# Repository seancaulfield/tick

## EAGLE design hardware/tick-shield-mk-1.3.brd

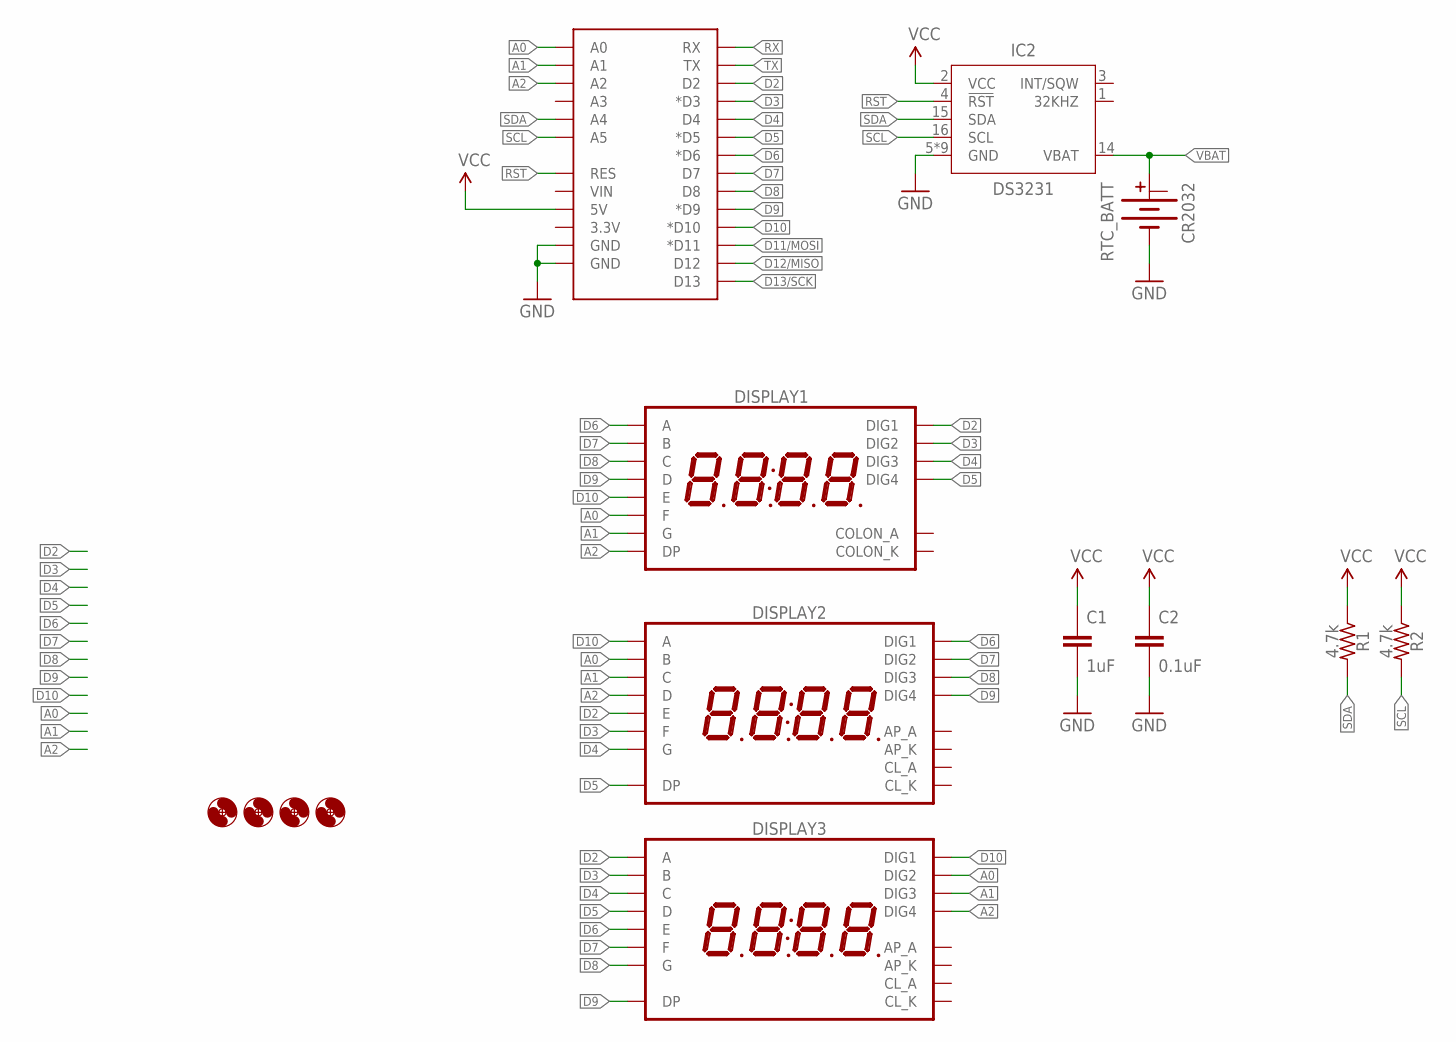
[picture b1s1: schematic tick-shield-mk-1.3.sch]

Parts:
C1: 1uF; C025-024X044
C2: 0.1uF; C025-024X044
DISPLAY1: 7SEG_4DIGIT_COLON14.2MM-CC-NS; 7SEG_4DIG_NS
DISPLAY2, DISPLAY3: 7SEG_4DIGIT_COLON_APOS; 7SEG_4DIG_10MM
H1, H2, H3, H4: HOLE#2; HOLE-#2
IC2: DS3231; SO16W
R1, R2: 4.7k; RESISTOR-AXIAL-PTH-6.35MM
RTC_BATT: CR2032; BATTCON_20MM_MINE
U$1: ARDUINO_SHIELD_SMALLER; ARDUINO_SHIELD_NOOUTLINE_INSIDE_SMALLER

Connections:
A0: DISPLAY1.P$12 (F), DISPLAY2.16 (B), DISPLAY3.2 (DIG2), U$1.A0
A1: DISPLAY1.P$5 (G), DISPLAY2.13 (C), DISPLAY3.6 (DIG3), U$1.A1
A2: DISPLAY1.P$3 (DP), DISPLAY2.3 (D), DISPLAY3.8 (DIG4), U$1.A2
D2: DISPLAY1.P$14 (DIG1), DISPLAY2.5 (E), DISPLAY3.14 (A), U$1.D2
D3: DISPLAY1.P$11 (DIG2), DISPLAY2.11 (F), DISPLAY3.16 (B), U$1.D3 (*D3)
D4: DISPLAY1.P$10 (DIG3), DISPLAY2.15 (G), DISPLAY3.13 (C), U$1.D4
D5: DISPLAY1.P$6 (DIG4), DISPLAY2.7 (DP), DISPLAY3.3 (D), U$1.D5 (*D5)
D6: DISPLAY1.P$13 (A), DISPLAY2.1 (DIG1), DISPLAY3.5 (E), U$1.D6 (*D6)
D7: DISPLAY1.P$9 (B), DISPLAY2.2 (DIG2), DISPLAY3.11 (F), U$1.D7
D8: DISPLAY1.P$4 (C), DISPLAY2.6 (DIG3), DISPLAY3.15 (G), U$1.D8
D9: DISPLAY1.P$2 (D), DISPLAY2.8 (DIG4), DISPLAY3.7 (DP), U$1.D9 (*D9)
D10: DISPLAY1.P$1 (E), DISPLAY2.14 (A), DISPLAY3.1 (DIG1), U$1.D10 (*D10)
D11/MOSI: U$1.D11 (*D11)
D12/MISO: U$1.D12
D13/SCK: U$1.D13
GND: C1.2, C2.2, IC2.5 (GND), IC2.6 (GND), IC2.7 (GND), IC2.8 (GND), IC2.9 (GND), IC2.10 (GND), IC2.11 (GND), IC2.12 (GND), IC2.13 (GND), RTC_BATT.BOTTOM (-), U$1.GND@0 (GND), U$1.GND@1 (GND)
RST: IC2.4 (!RST), U$1.RES
RX: U$1.RX
SCL: IC2.16 (SCL), R2.P$2 (2), U$1.A5
SDA: IC2.15 (SDA), R1.P$2 (2), U$1.A4
TX: U$1.TX
VBAT: IC2.14 (VBAT), RTC_BATT.TOP@1 (+)
VCC: C1.1, C2.1, IC2.2 (VCC), R1.P$1 (1), R2.P$1 (1), U$1.5V

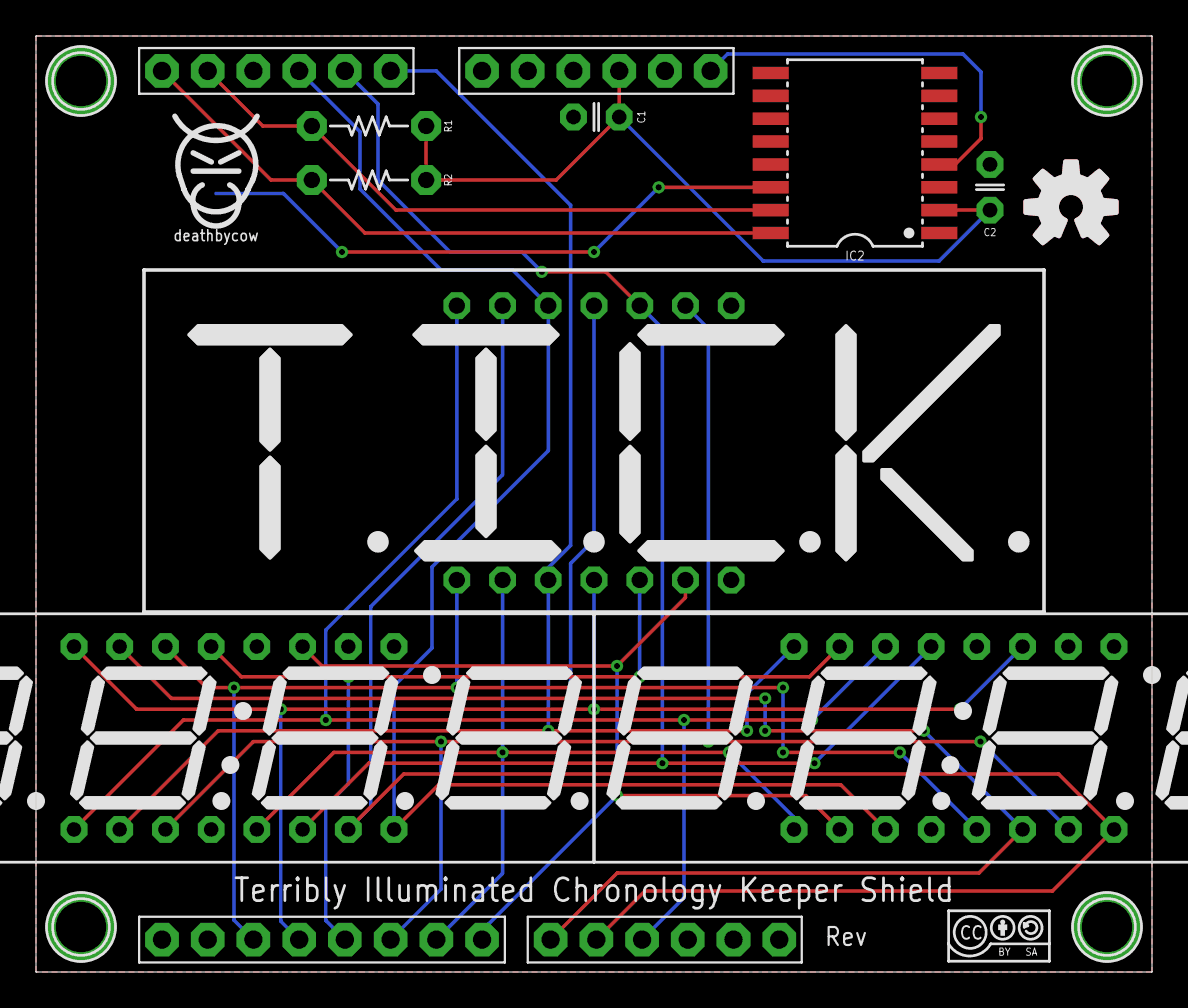
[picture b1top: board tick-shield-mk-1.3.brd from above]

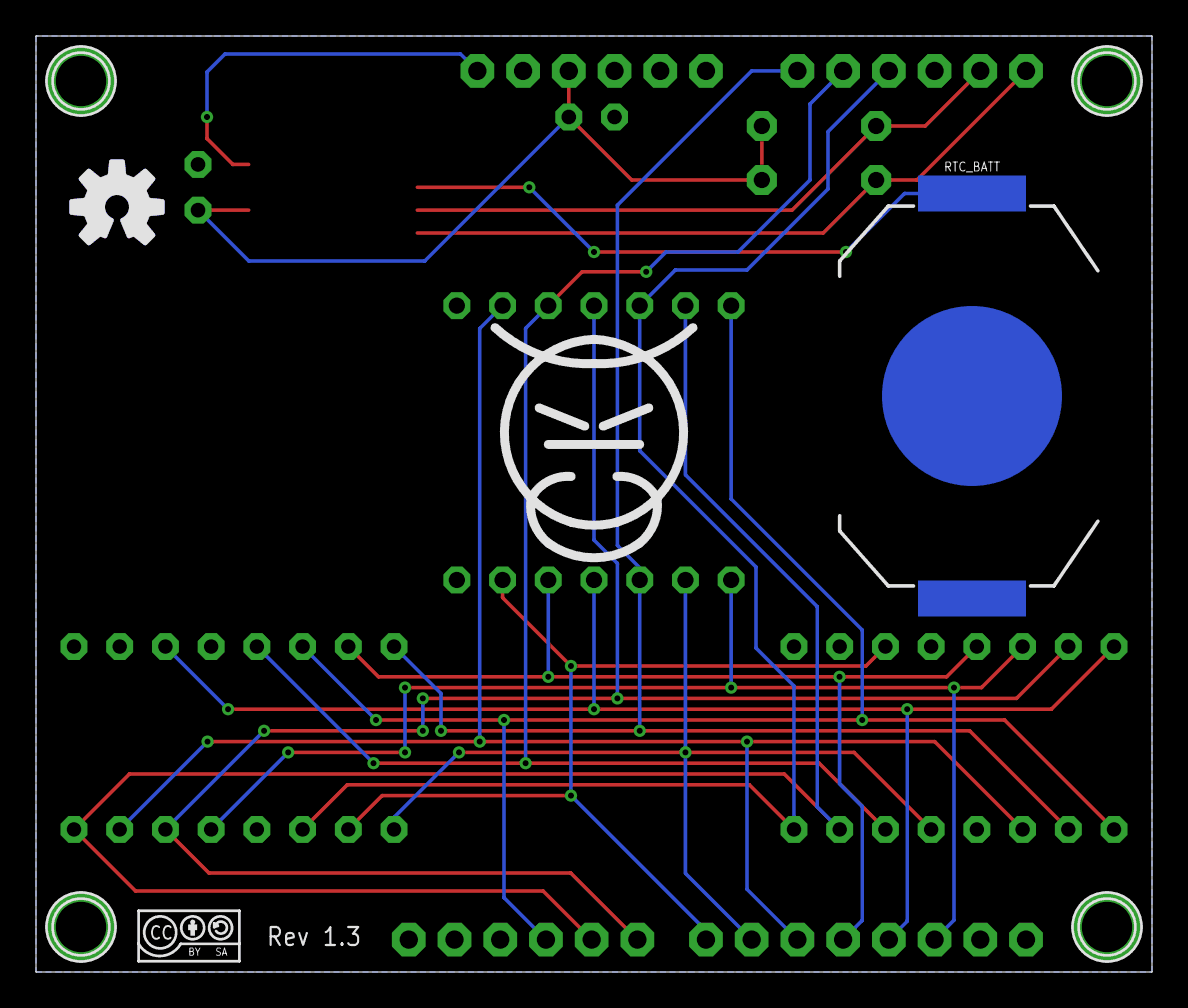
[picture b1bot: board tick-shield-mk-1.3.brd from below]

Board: 2 copper layers, 62.0 x 52.0 mm, 21 parts (4 on the bottom side), 18 nets.

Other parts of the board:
U$2: TICK_SYMBOL_0.56
U$3, U$4: CC-BY-SA-4.0-NO-URL
U$5: COW
U$6: COW_SMALL
U$7, U$8: OSHWLOGO_TOP_0.2_A

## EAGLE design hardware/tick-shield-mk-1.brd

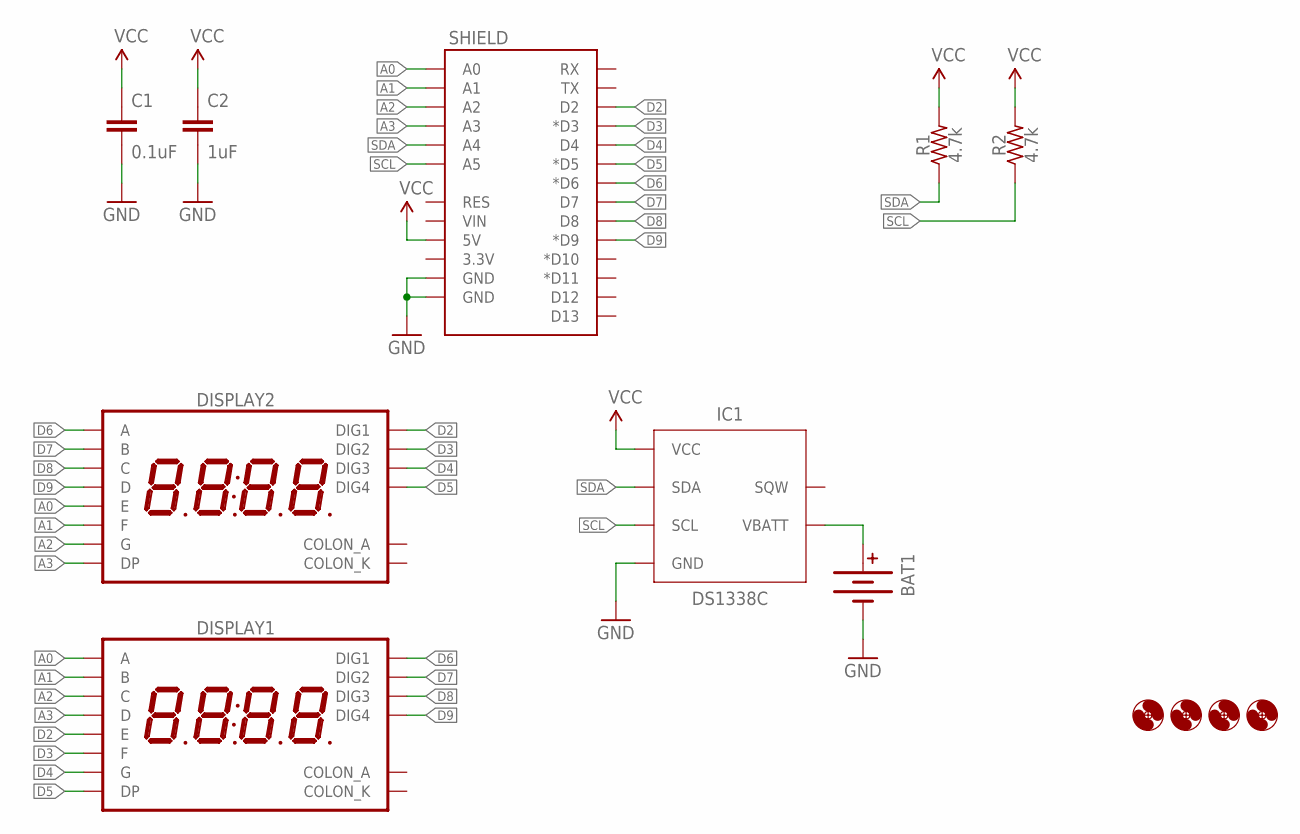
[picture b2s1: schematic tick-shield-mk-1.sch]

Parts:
BAT1: BATTERY12MM; BATTCON_12MM
C1: 0.1uF; C0603
C2: 1uF; C0805
DISPLAY1, DISPLAY2: 7SEG_4DIGIT_COLON14.2MM-CC; 7SEG_4DIG_0.56IN_14MM_ADAFRUIT
H1, H2, H3, H4: HOLE#2; HOLE-#2
IC1: DS1338C; SO16W
R1, R2: 4.7k; R0603
SHIELD: ARDUINO_SHIELD_SMALLER; ARDUINO_SHIELD_NOOUTLINE_INSIDE_SMALLER

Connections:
A0: DISPLAY1.P$13 (A), DISPLAY2.P$1 (E), SHIELD.A0
A1: DISPLAY1.P$9 (B), DISPLAY2.P$12 (F), SHIELD.A1
A2: DISPLAY1.P$4 (C), DISPLAY2.P$5 (G), SHIELD.A2
A3: DISPLAY1.P$2 (D), DISPLAY2.P$3 (DP), SHIELD.A3
D2: DISPLAY1.P$1 (E), DISPLAY2.P$14 (DIG1), SHIELD.D2
D3: DISPLAY1.P$12 (F), DISPLAY2.P$11 (DIG2), SHIELD.D3 (*D3)
D4: DISPLAY1.P$5 (G), DISPLAY2.P$10 (DIG3), SHIELD.D4
D5: DISPLAY1.P$3 (DP), DISPLAY2.P$6 (DIG4), SHIELD.D5 (*D5)
D6: DISPLAY1.P$14 (DIG1), DISPLAY2.P$13 (A), SHIELD.D6 (*D6)
D7: DISPLAY1.P$11 (DIG2), DISPLAY2.P$9 (B), SHIELD.D7
D8: DISPLAY1.P$10 (DIG3), DISPLAY2.P$4 (C), SHIELD.D8
D9: DISPLAY1.P$6 (DIG4), DISPLAY2.P$2 (D), SHIELD.D9 (*D9)
GND: BAT1.GND (-), C1.2, C2.2, IC1.4 (GND), IC1.5 (GND), IC1.6 (GND), IC1.7 (GND), IC1.8 (GND), IC1.9 (GND), IC1.10 (GND), IC1.11 (GND), IC1.12 (GND), IC1.13 (GND), IC1.15 (GND), SHIELD.GND@0 (GND), SHIELD.GND@1 (GND)
unnamed: BAT1.PWR@1 (+), IC1.14 (VBATT)
SCL: IC1.1 (SCL), R2.1, SHIELD.A5
SDA: IC1.16 (SDA), R1.1, SHIELD.A4
VCC: C1.1, C2.1, IC1.3 (VCC), R1.2, R2.2, SHIELD.5V

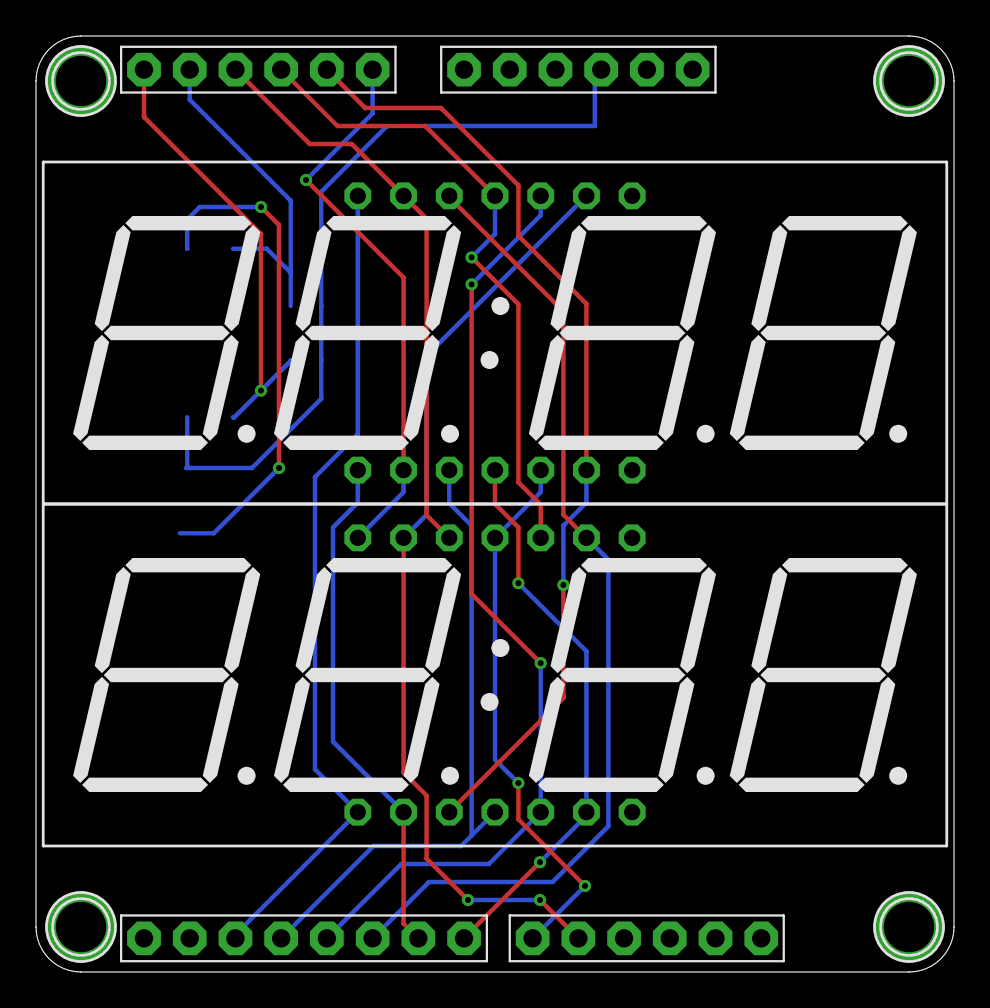
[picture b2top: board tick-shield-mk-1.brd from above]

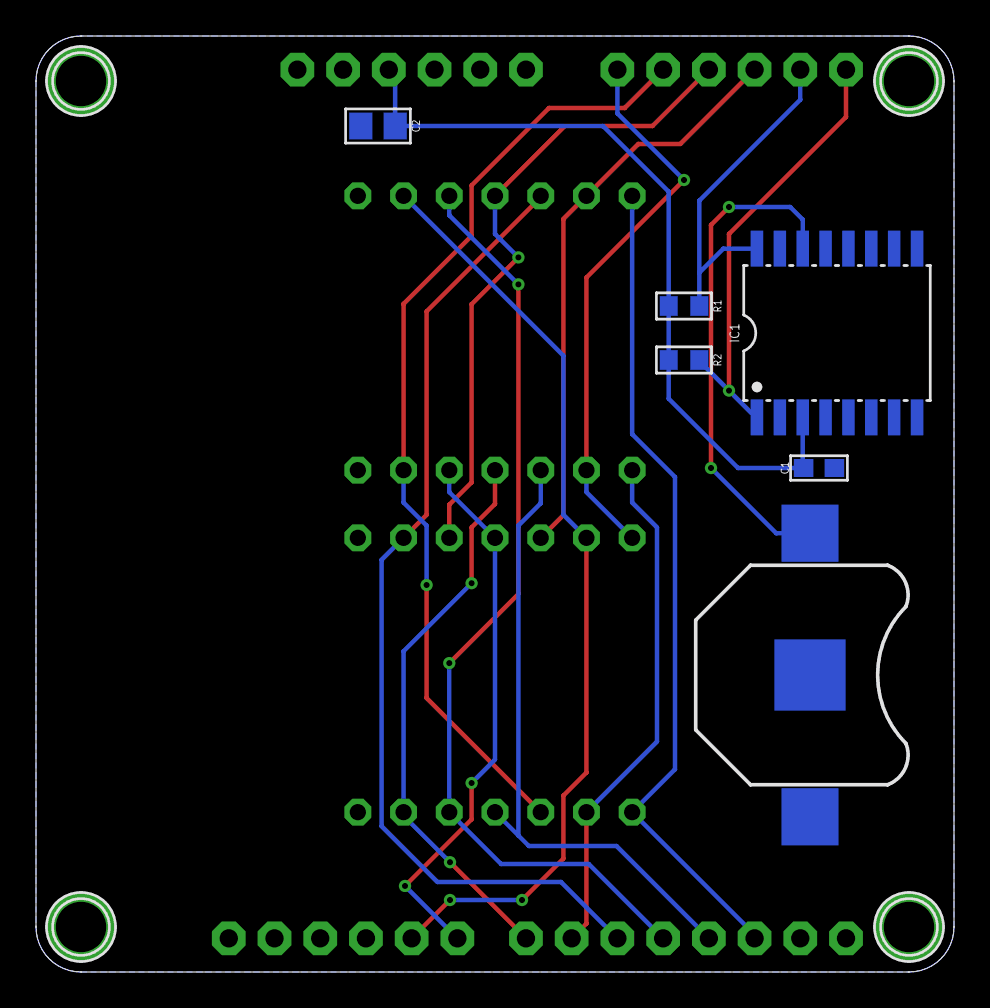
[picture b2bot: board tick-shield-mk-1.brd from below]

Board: 2 copper layers, 51.0 x 52.0 mm, 13 parts (6 on the bottom side), 17 nets.

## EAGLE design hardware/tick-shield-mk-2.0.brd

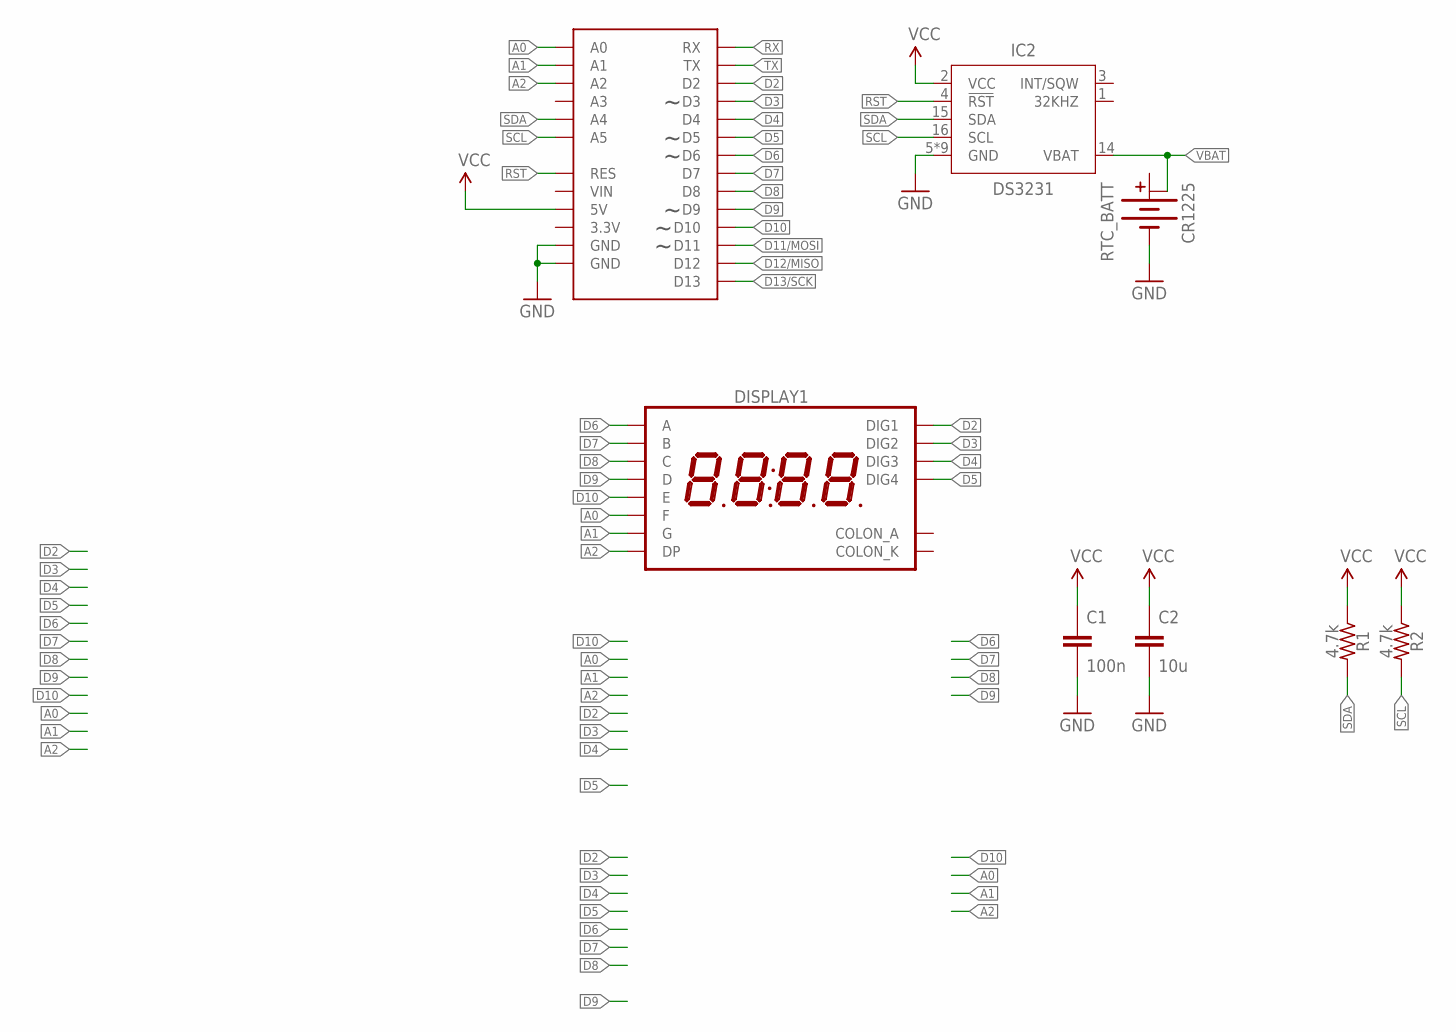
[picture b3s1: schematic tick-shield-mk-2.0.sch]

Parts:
C1: 100n; C025-024X044
C2: 10u; C050-025X075
DISPLAY1: 7SEG_4DIGIT_COLONTICK; 7SEG_4DIG_TICK
IC2: DS3231; SO16W
R1, R2: 4.7k; RESISTOR-AXIAL-PTH-7.62MM
RTC_BATT: CR1225; BATTCON_12MM_PTH3
U$1: ARDUINO_SHIELD_SMALLER; ARDUINO_SHIELD_NOOUTLINE_INSIDE_SMALLER

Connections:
A0: DISPLAY1.P$12 (F), U$1.A0
A1: DISPLAY1.P$5 (G), U$1.A1
A2: DISPLAY1.P$3 (DP), U$1.A2
D2: DISPLAY1.P$14 (DIG1), U$1.D2
D3: DISPLAY1.P$11 (DIG2), U$1.D3
D4: DISPLAY1.P$10 (DIG3), U$1.D4
D5: DISPLAY1.P$6 (DIG4), U$1.D5
D6: DISPLAY1.P$13 (A), U$1.D6
D7: DISPLAY1.P$9 (B), U$1.D7
D8: DISPLAY1.P$4 (C), U$1.D8
D9: DISPLAY1.P$2 (D), U$1.D9
D10: DISPLAY1.P$1 (E), U$1.D10
D11/MOSI: U$1.D11
D12/MISO: U$1.D12
D13/SCK: U$1.D13
GND: C1.2, C2.2, IC2.5 (GND), IC2.6 (GND), IC2.7 (GND), IC2.8 (GND), IC2.9 (GND), IC2.10 (GND), IC2.11 (GND), IC2.12 (GND), IC2.13 (GND), RTC_BATT.-, U$1.GND@0 (GND), U$1.GND@1 (GND)
RST: IC2.4 (!RST), U$1.RES
RX: U$1.RX
SCL: IC2.16 (SCL), R2.P$2 (2), U$1.A5
SDA: IC2.15 (SDA), R1.P$2 (2), U$1.A4
TX: U$1.TX
VBAT: IC2.14 (VBAT), RTC_BATT.+@3 (+1), RTC_BATT.+@4 (+1)
VCC: C1.1, C2.1, IC2.2 (VCC), R1.P$1 (1), R2.P$1 (1), U$1.5V

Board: 2 copper layers, 12 parts (2 on the bottom side), 18 nets, no tracks yet.

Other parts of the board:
U$3, U$4: CC-BY-SA-4.0-NO-URL
U$7, U$8: OSHWLOGO_TOP_0.2_A

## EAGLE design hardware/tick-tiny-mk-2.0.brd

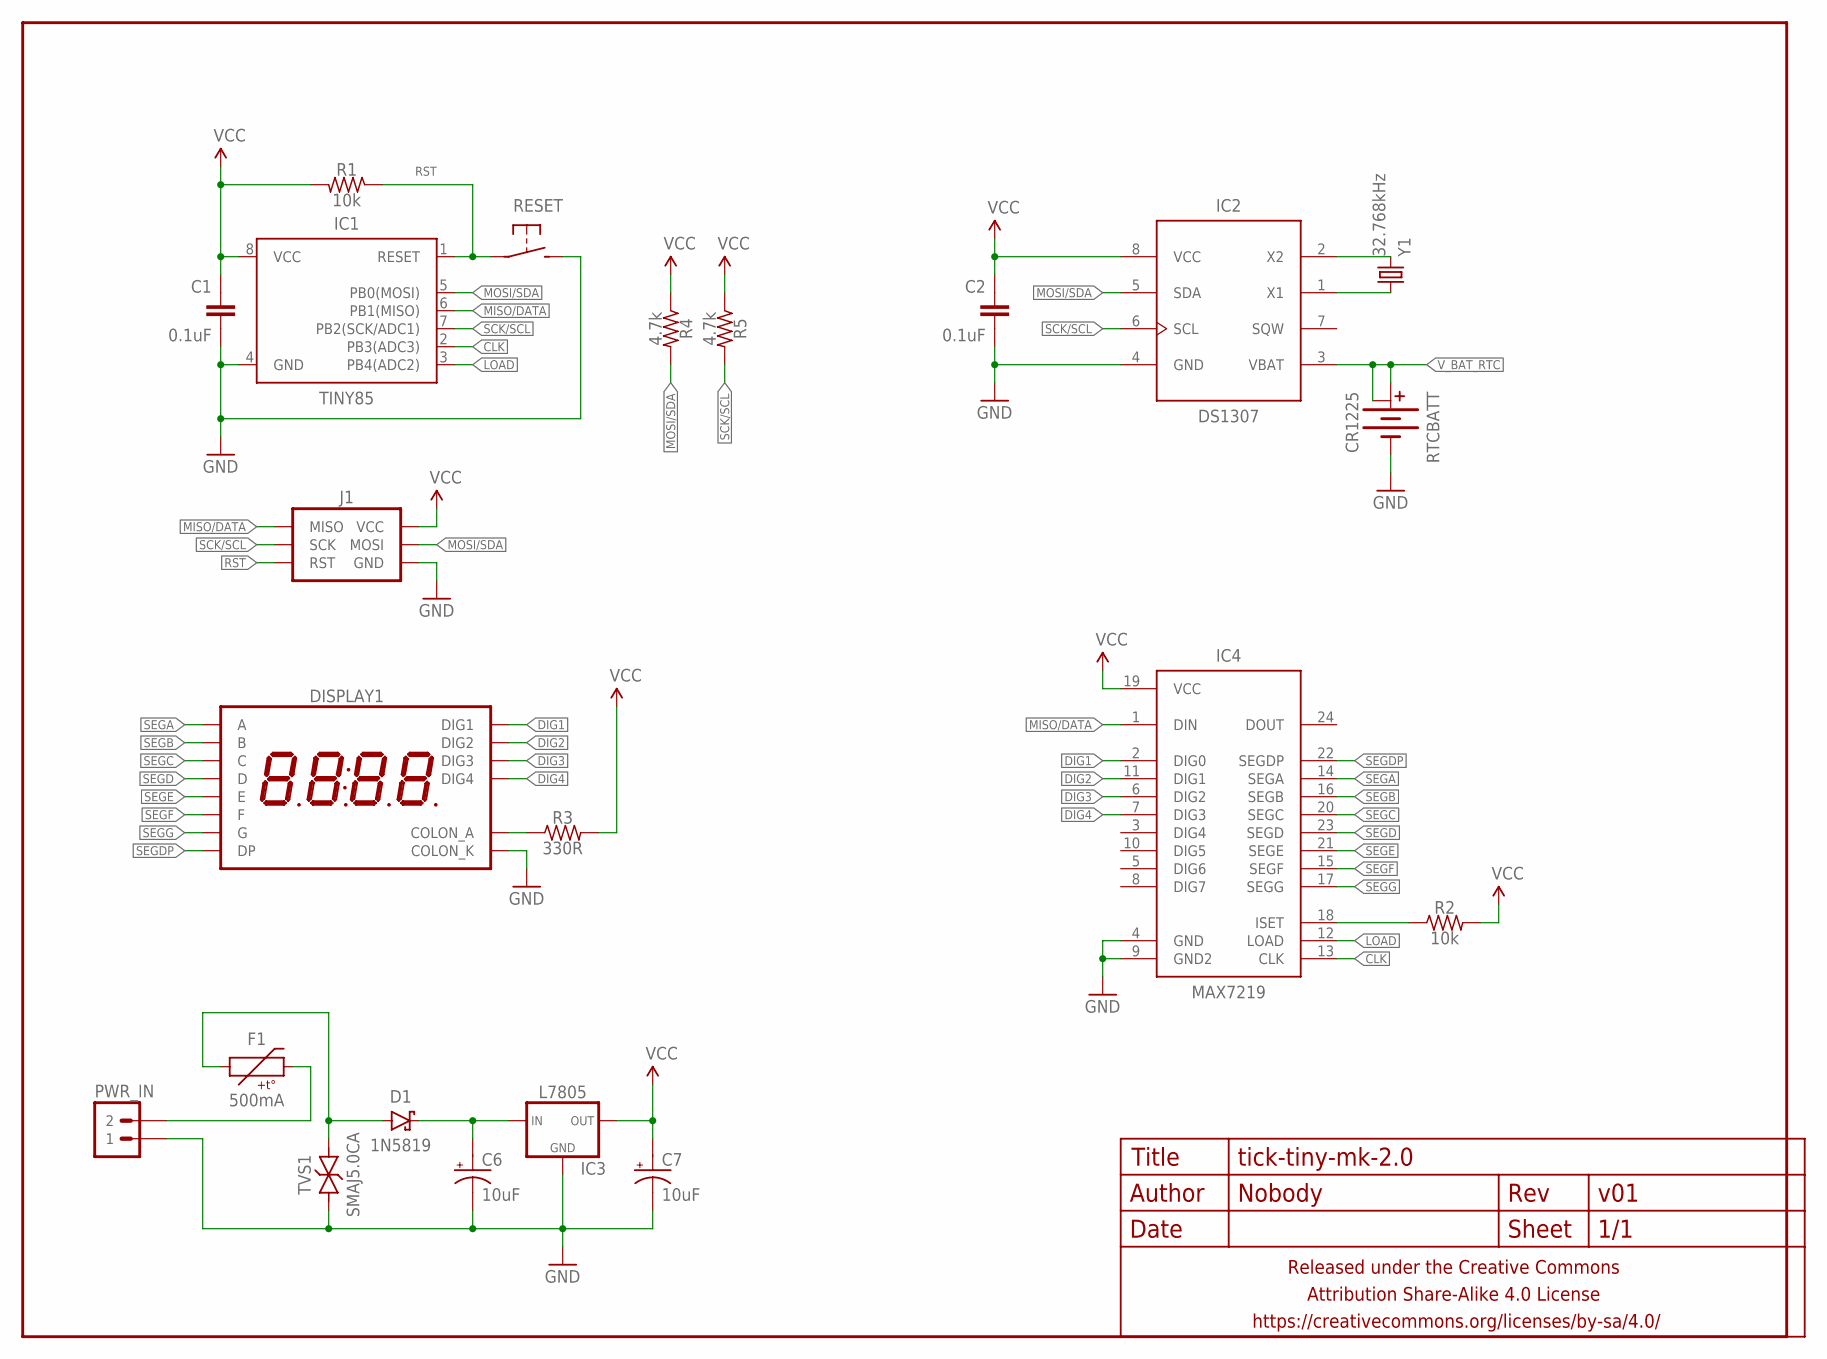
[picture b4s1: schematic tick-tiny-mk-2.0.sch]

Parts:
C1, C2: 0.1uF; C025-024X044
C6, C7: 10uF; E2-5
D1: 1N5819; DIODE-10.16MM
DISPLAY1: 7SEG_4DIGIT_COLON14.2MM-CC-NS; 7SEG_4DIG_NS
F1: 500mA; PTC-PTH-5.08MM
FRAME1: FRAME-LETTERNO_PACKAGE; DUMMY
IC1: TINY85; DIP08
IC2: DS1307; DIL08
IC3: L7805; TO-92-AMMO
IC4: MAX7219; SO24W
J1: AVR_SPI_PRG_6PTH; 2X3
PWR_IN: M02JST-PTH-RA-R+; JST-2-PH-RA-PTH-R+
R1: 10k; RESISTOR-AXIAL-PTH-7.62MM
R2: 10k; RESISTOR-AXIAL-PTH-5.08MM
R3: 330R; RESISTOR-AXIAL-PTH-5.08MM
R4, R5: 4.7k; RESISTOR-AXIAL-PTH-7.62MM
RESET: SPST-NO-TACT3MM-PTH-SMALL-PADS; DTS-3-SMALL-PADS
RTCBATT: CR1225; BATTCON_12MM_SMD
TVS1: SMAJ5.0CA; DO-41-TVS-BI-10.16MM
Y1: 32.768kHz; TC26H

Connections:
CLK: IC1.2 (PB3(ADC3)), IC4.13 (CLK)
DIG1: DISPLAY1.P$14 (DIG1), IC4.2 (DIG0)
DIG2: DISPLAY1.P$11 (DIG2), IC4.11 (DIG1)
DIG3: DISPLAY1.P$10 (DIG3), IC4.6 (DIG2)
DIG4: DISPLAY1.P$6 (DIG4), IC4.7 (DIG3)
GND: C1.2, C2.2, C6.-, C7.-, DISPLAY1.P$7 (COLON_K), IC1.4 (GND), IC2.4 (GND), IC3.2 (GND), IC4.4 (GND), IC4.9 (GND2), J1.6 (GND), PWR_IN.1, RESET.2, RTCBATT.-, TVS1.P$1 (1)
LOAD: IC1.3 (PB4(ADC2)), IC4.12 (LOAD)
MISO/DATA: IC1.6 (PB1(MISO)), IC4.1 (DIN), J1.1 (MISO)
MOSI/SDA: IC1.5 (PB0(MOSI)), IC2.5 (SDA), J1.4 (MOSI), R4.P$2 (2)
unnamed: IC2.2 (X2), Y1.2
unnamed: IC2.1 (X1), Y1.1
unnamed: D1.A, F1.P$1 (1), TVS1.P$2 (2)
unnamed: IC4.18 (ISET), R2.P$1 (1)
unnamed: F1.P$2 (2), PWR_IN.2
unnamed: DISPLAY1.P$8 (COLON_A), R3.P$1 (1)
unnamed: C6.+, D1.C, IC3.1 (IN)
RST: IC1.1 (RESET), J1.5 (RST), R1.P$1 (1), RESET.1
SCK/SCL: IC1.7 (PB2(SCK/ADC1)), IC2.6 (SCL), J1.3 (SCK), R5.P$2 (2)
SEGA: DISPLAY1.P$13 (A), IC4.14 (SEGA)
SEGB: DISPLAY1.P$9 (B), IC4.16 (SEGB)
SEGC: DISPLAY1.P$4 (C), IC4.20 (SEGC)
SEGD: DISPLAY1.P$2 (D), IC4.23 (SEGD)
SEGDP: DISPLAY1.P$3 (DP), IC4.22 (SEGDP)
SEGE: DISPLAY1.P$1 (E), IC4.21 (SEGE)
SEGF: DISPLAY1.P$12 (F), IC4.15 (SEGF)
SEGG: DISPLAY1.P$5 (G), IC4.17 (SEGG)
VCC: C1.1, C2.1, C7.+, IC1.8 (VCC), IC2.8 (VCC), IC3.3 (OUT), IC4.19 (VCC), J1.2 (VCC), R1.P$2 (2), R2.P$2 (2), R3.P$2 (2), R4.P$1 (1), R5.P$1 (1)
V_BAT_RTC: IC2.3 (VBAT), RTCBATT.+@1 (+), RTCBATT.+@2 (+1)

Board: 2 copper layers, 28 parts (4 on the bottom side), 28 nets, no tracks yet.

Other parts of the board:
U$1, U$5: CC-BY-SA-4.0-NO-URL
U$2, U$4: COW_SMALL_METAL_NOTEXT
U$3: OSHWLOGO_TOP_0.2

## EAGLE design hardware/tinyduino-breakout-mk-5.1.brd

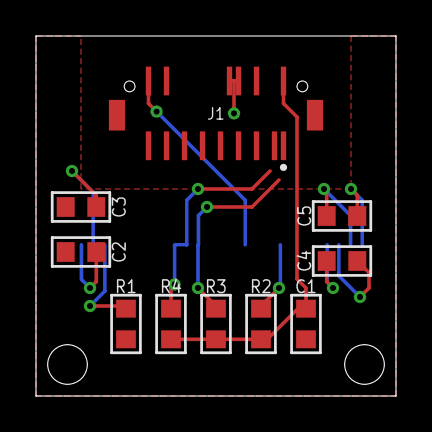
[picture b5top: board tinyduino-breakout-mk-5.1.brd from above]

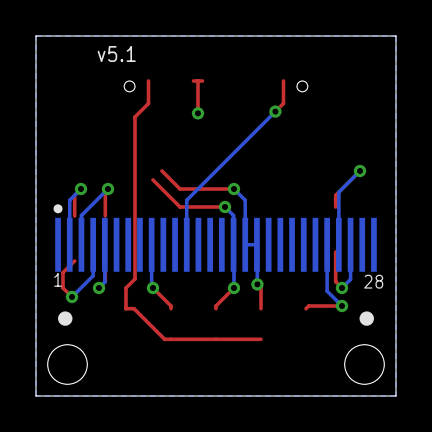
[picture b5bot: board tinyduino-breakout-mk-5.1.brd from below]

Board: 2 copper layers, 20.0 x 20.0 mm, 12 parts (3 on the bottom side), 13 nets.

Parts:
C1, C4, C5: 1u; C0603
C2: 2u2; C0603
C3: 4u7; C0603
DISP1: ER-OLED0.66-1FOLDED-SAME; ER-OLED0.66-1-FOLDED-SAME
FRAME1: FRAME-LETTERNO_PACKAGE; DUMMY
J1: DF12-32-DP-NOTREALLYREV; DF12-32-DP-I2C+EXTRA-REV
R1: 390K; R0603
R2: 100K; R0603
R3, R4: 4K7; R0603

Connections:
DRST: DISP1.12, J1.32
GND: C1.2, C2.2, C3.2, DISP1.7, DISP1.10, DISP1.13, DISP1.27, J1.12, J1.14, R1.1
unnamed: C2.1, DISP1.26
unnamed: C3.1, DISP1.25
unnamed: DISP1.24, R1.2
unnamed: C4.1, DISP1.4
unnamed: C4.2, DISP1.5
unnamed: C5.1, DISP1.2
unnamed: C5.2, DISP1.3
unnamed: DISP1.9, R2.1
SCL: DISP1.16, J1.1, R3.1
SDA: DISP1.17, DISP1.18, J1.3, R4.1
VCC: C1.1, DISP1.6, DISP1.8, J1.2, R2.2, R3.2, R4.2

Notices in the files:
parts and their libraries:
A_butts: Released under the Creative Commons Attribution Share-Alike 4.0 License
A_butts: https://creativecommons.org/licenses/by-sa/4.0
A_butts: Released under the Creative Commons
